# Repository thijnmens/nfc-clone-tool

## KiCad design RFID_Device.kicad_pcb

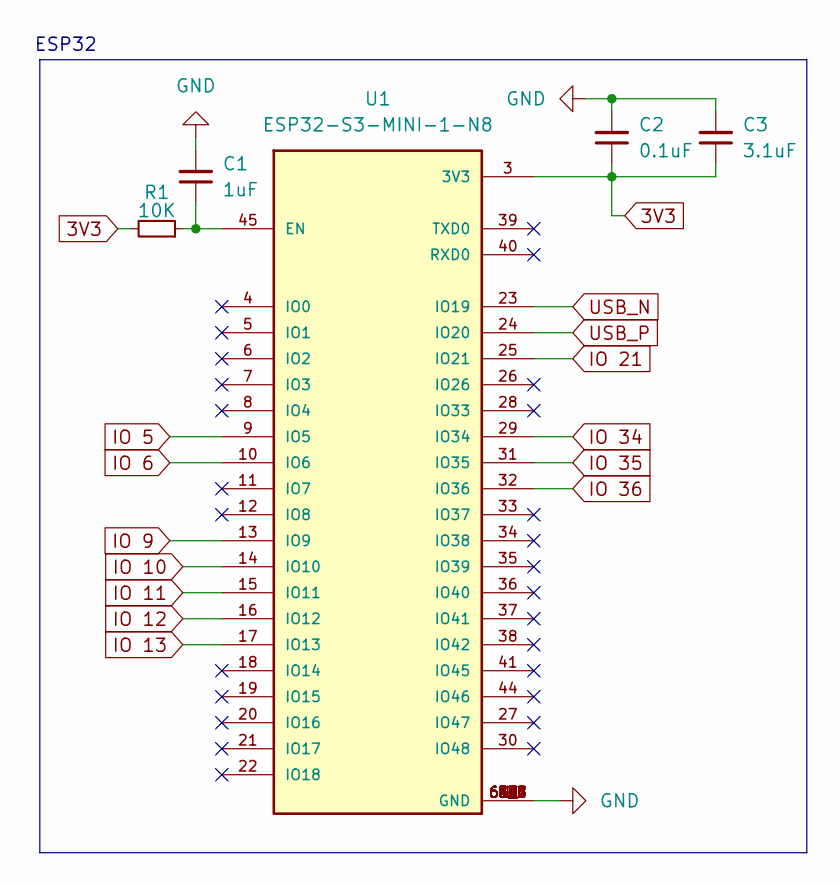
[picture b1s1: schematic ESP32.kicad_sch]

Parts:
C1: 1uF; C_0603_1608Metric; Manufacturer_Part_Number CC0603KRX5R8BB105; DigiKey_Part_Number 311-1445-1-ND
C2: 0.1uF; C_0603_1608Metric; Manufacturer_Part_Number CC0603KRX7R8BB104; DigiKey_Part_Number 311-1341-1-ND
C3: 3.1uF; C_0805_2012Metric; Manufacturer_Part_Number CC0805ZKY5V6BB335; DigiKey_Part_Number 311-1190-1-ND
R1: 10K; R_0402_1005Metric; Manufacturer_Part_Number RC0402JR-0710KL; DigiKey_Part_Number 311-10KJRCT-ND
U1: ESP32-S3-MINI-1-N8; XCVR_ESP32-S3-MINI-1-N8; Manufacturer_Part_Number ESP32-S3-MINI-1-N8; DigiKey_Part_Number 1965-ESP32-S3-MINI-1-N8CT-ND

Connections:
3V3: C2.1, C3.1, R1.2, U1.3 (3V3); also elsewhere on the board
GND: C1.2, C2.2, C3.2, U1.1 (GND), U1.2 (GND), U1.42 (GND), U1.43 (GND), U1.46 (GND), U1.47 (GND), U1.48 (GND), U1.49 (GND), U1.50 (GND), U1.51 (GND), U1.52 (GND), U1.53 (GND), U1.54 (GND), U1.55 (GND), U1.56 (GND), U1.57 (GND), U1.58 (GND), U1.59 (GND), U1.60 (GND), U1.61 (GND), U1.61_1 (GND), U1.61_2 (GND), U1.61_3 (GND), U1.61_4 (GND), U1.61_5 (GND), U1.61_6 (GND), U1.61_7 (GND), U1.61_8 (GND), U1.62 (GND), U1.63 (GND), U1.64 (GND), U1.65 (GND); also elsewhere on the board
IO 5: U1.9 (IO5); also elsewhere on the board
IO 6: U1.10 (IO6); also elsewhere on the board
IO 9: U1.13 (IO9); also elsewhere on the board
IO 10: U1.14 (IO10); also elsewhere on the board
IO 11: U1.15 (IO11); also elsewhere on the board
IO 12: U1.16 (IO12); also elsewhere on the board
IO 13: U1.17 (IO13); also elsewhere on the board
IO 21: U1.25 (IO21); also elsewhere on the board
IO 34: U1.29 (IO34); also elsewhere on the board
IO 35: U1.31 (IO35); also elsewhere on the board
IO 36: U1.32 (IO36); also elsewhere on the board
unnamed: C1.1, R1.1, U1.45 (EN)
USB_N: U1.23 (IO19); also elsewhere on the board
USB_P: U1.24 (IO20); also elsewhere on the board

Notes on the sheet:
ESP32

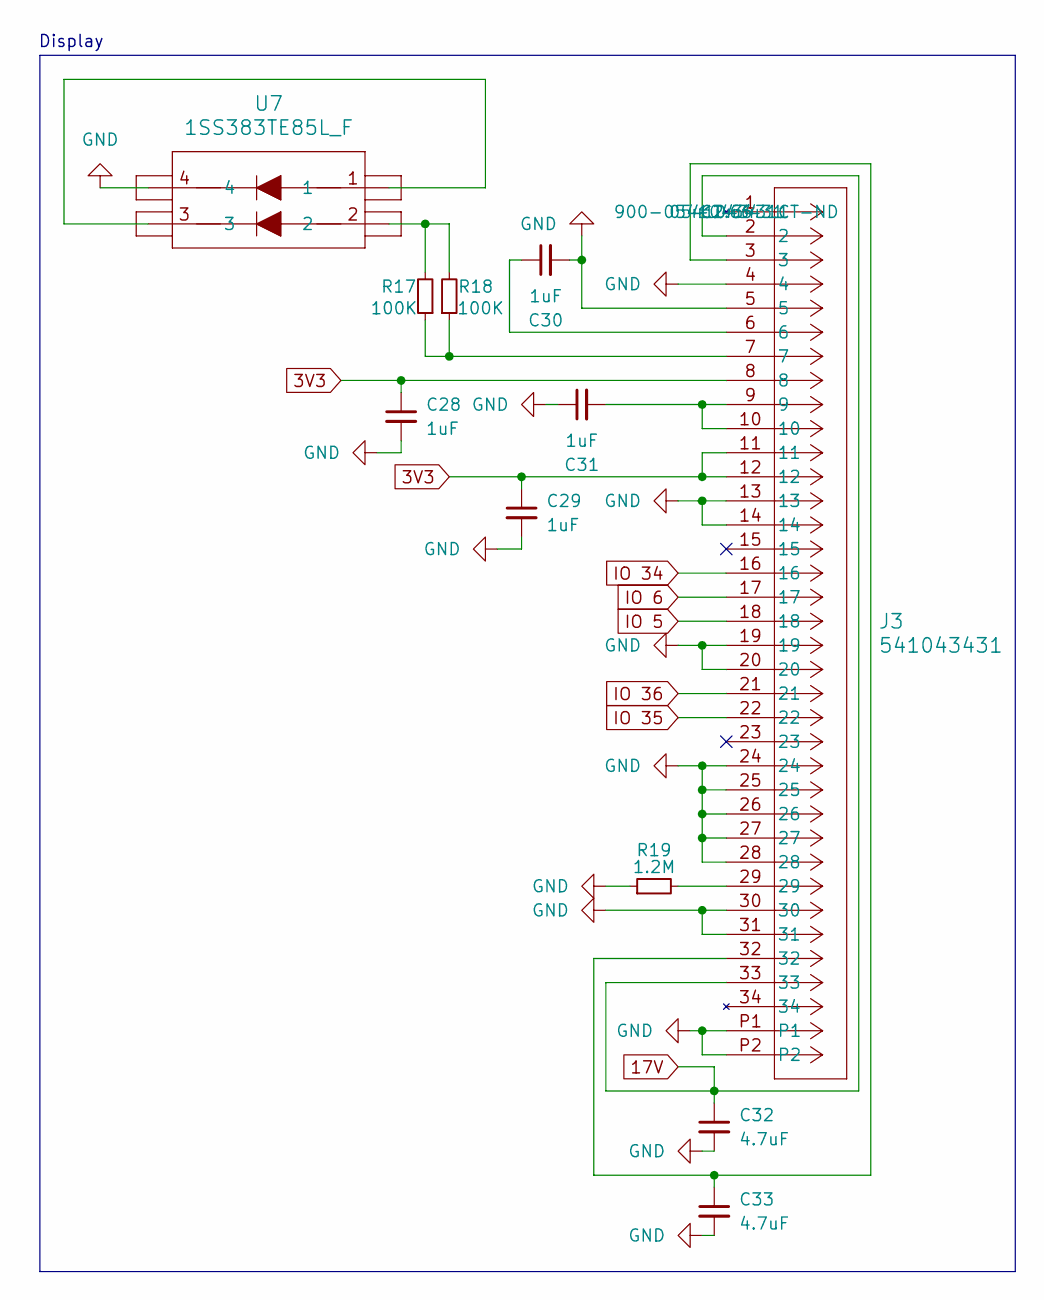
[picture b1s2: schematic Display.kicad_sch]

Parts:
C28, C29, C30, C31: 1uF; C_0603_1608Metric; Manufacturer_Part_Number CC0603KRX5R8BB105; DigiKey_Part_Number 311-1445-1-ND
C32, C33: 4.7uF; C_0805_2012Metric; Manufacturer_Part_Number CL21A475KAQNNNE; DigiKey_Part_Number 1276-1244-1-ND
J3: 541043431; CON_541043431_MOL; Manufacturer_Part_Number 0541043431; DigiKey_Part_Number 900-0541043431CT-ND
R17, R18: 100K; R_0402_1005Metric; Manufacturer_Part_Number RC0402FR-07100KL; DigiKey_Part_Number 311-100KLRCT-ND
R19: 1.2M; R_0402_1005Metric; Manufacturer_Part_Number AC0402FR-071M2L; DigiKey_Part_Number YAG5649CT-ND
U7: 1SS383TE85L_F; USQ_TOS; Manufacturer_Part_Number 1SS383(TE85L,F); DigiKey_Part_Number 1SS383(TE85LF)CT-ND

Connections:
3V3: C28.1, C29.1, J3.8, J3.11, J3.12; also elsewhere on the board
17V: C32.1, J3.2, J3.33; also elsewhere on the board
GND: C28.2, C29.2, C30.2, C31.1, C32.2, C33.2, J3.4, J3.5, J3.13, J3.14, J3.19, J3.20, J3.24, J3.25, J3.26, J3.27, J3.28, J3.30, J3.31, J3.P1, J3.P2, R19.1, U7.4; also elsewhere on the board
IO 5: J3.18; also elsewhere on the board
IO 6: J3.17; also elsewhere on the board
IO 34: J3.16; also elsewhere on the board
IO 35: J3.22; also elsewhere on the board
IO 36: J3.21; also elsewhere on the board
unnamed: C30.1, J3.6
unnamed: C31.2, J3.9, J3.10
unnamed: C33.1, J3.3, J3.32
unnamed: J3.7, R17.1, R18.1
unnamed: J3.29, R19.2
unnamed: R17.2, R18.2, U7.2
unnamed: U7.1, U7.3

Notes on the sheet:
Display

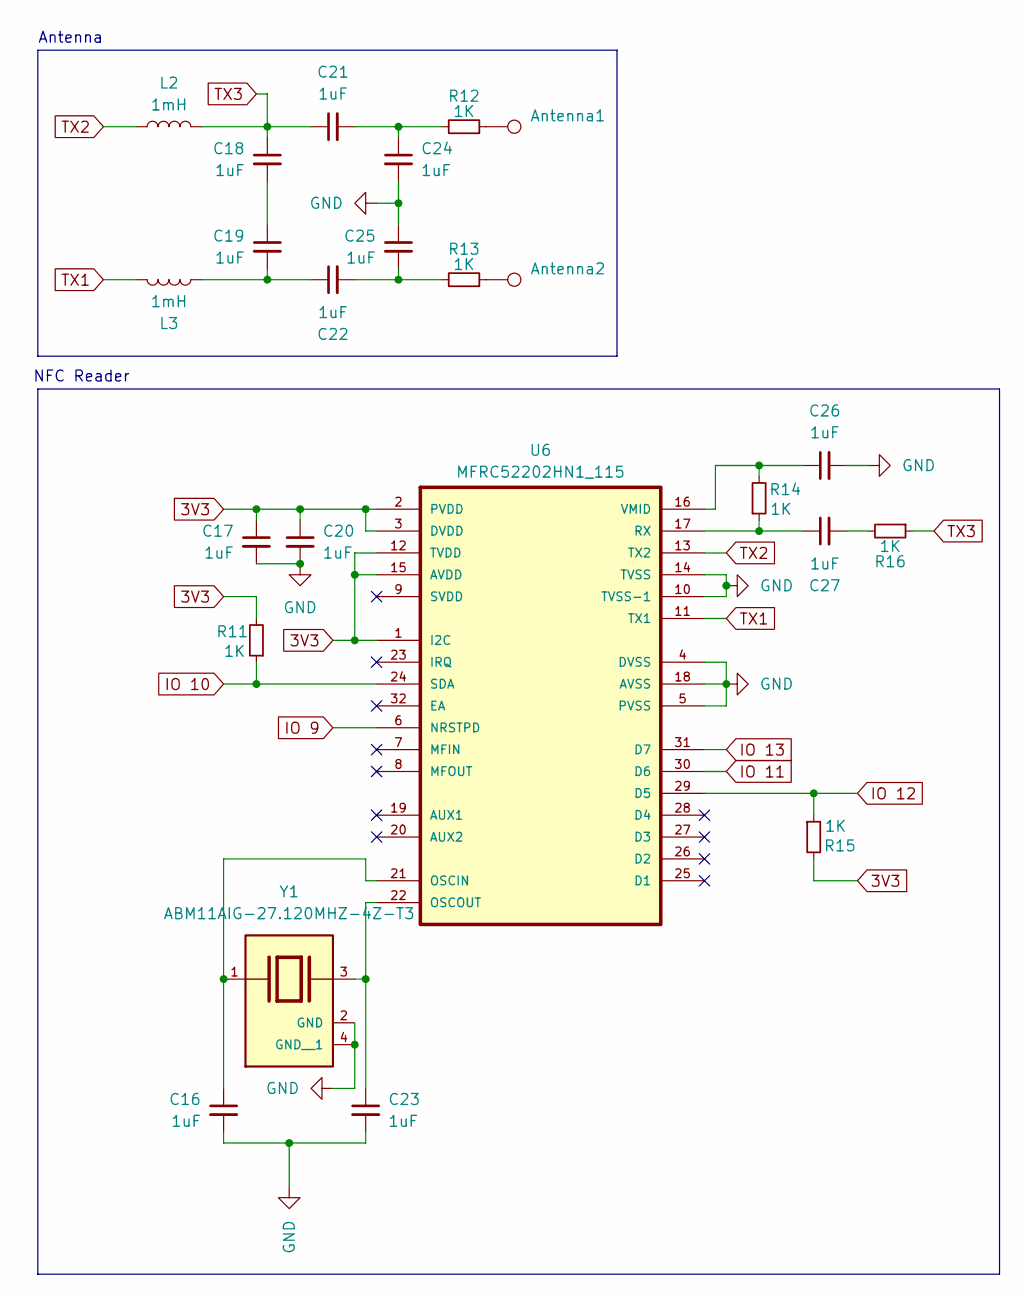
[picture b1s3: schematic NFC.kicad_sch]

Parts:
Antenna1, Antenna2: TestPoint_Pad_D2.0mm
C16, C17, C18, C19, C20, C21, C22, C23, C24, C25, C26, C27: 1uF; C_0603_1608Metric; Manufacturer_Part_Number CC0603KRX5R8BB105; DigiKey_Part_Number 311-1445-1-ND
L2, L3: 1mH; L_1210_3225Metric; Manufacturer_Part_Number CBC3225T102KR; DigiKey_Part_Number 587-3214-1-ND
R11, R12, R13, R14, R15, R16: 1K; R_1206_3216Metric; Manufacturer_Part_Number RNCP1206FTD1K00; DigiKey_Part_Number RNCP1206FTD1K00CT-ND
U6: MFRC52202HN1_115; HVQFN-32-1EP_5x5mm_P0.5mm_EP3.1x3.1mm; Manufacturer_Part_Number MFRC52202HN1,115; DigiKey_Part_Number 568-15200-1-ND
Y1: ABM11AIG-27.120MHZ-4Z-T3; XTAL_ABM11AIG-27.120MHZ-4Z-T3; Manufacturer_Part_Number ABM11AIG-27.120MHZ-4Z-T3; DigiKey_Part_Number 535-13376-1-ND

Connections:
3V3: C17.1, C20.1, R11.2, R15.2, U6.1 (I2C), U6.2 (PVDD), U6.3 (DVDD), U6.12 (TVDD), U6.15 (AVDD); also elsewhere on the board
GND: C16.2, C17.2, C20.2, C23.2, C24.2, C25.1, C26.2, U6.4 (DVSS), U6.5 (PVSS), U6.10 (TVSS-1), U6.14 (TVSS), U6.18 (AVSS), Y1.2 (GND), Y1.4 (GND__1); also elsewhere on the board
IO 9: U6.6 (NRSTPD); also elsewhere on the board
IO 10: R11.1, U6.24 (SDA); also elsewhere on the board
IO 11: U6.30 (D6); also elsewhere on the board
IO 12: R15.1, U6.29 (D5); also elsewhere on the board
IO 13: U6.31 (D7); also elsewhere on the board
unnamed: Antenna1.1, R12.1
unnamed: Antenna2.1, R13.1
unnamed: C18.2, C19.1
unnamed: C19.2, C22.1, L3.2
unnamed: C21.2, C24.1, R12.2
unnamed: C22.2, C25.2, R13.2
unnamed: C27.2, R16.2
unnamed: C16.1, U6.21 (OSCIN), Y1.1
unnamed: C23.1, U6.22 (OSCOUT), Y1.3
unnamed: C27.1, R14.1, U6.17 (RX)
unnamed: C26.1, R14.2, U6.16 (VMID)
TX1: L3.1, U6.11 (TX1)
TX2: L2.1, U6.13 (TX2)
TX3: C18.1, C21.1, L2.2, R16.1

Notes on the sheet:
NFC Reader
Antenna

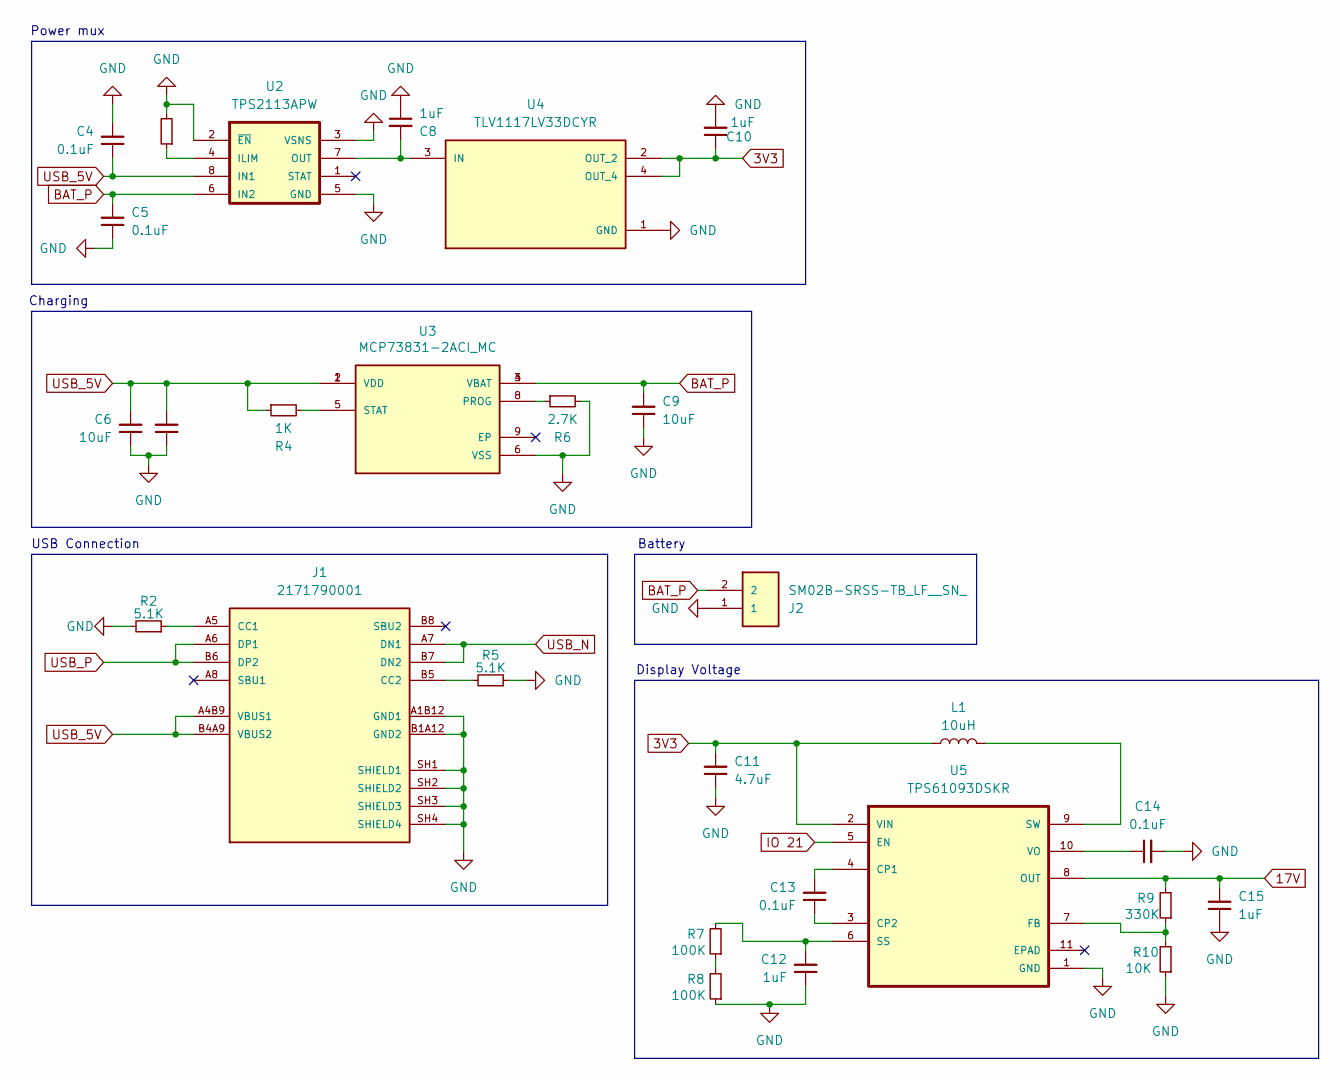
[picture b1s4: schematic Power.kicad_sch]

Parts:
C4, C5, C7, C13, C14: 0.1uF; C_0603_1608Metric; Manufacturer_Part_Number CC0603KRX7R8BB104; DigiKey_Part_Number 311-1341-1-ND
C6, C9: 10uF; C_0805_2012Metric; Manufacturer_Part_Number CL21A106KOQNNNG; DigiKey_Part_Number 1276-6455-1-ND
C8, C10, C12, C15: 1uF; C_0603_1608Metric; Manufacturer_Part_Number CC0603KRX5R8BB105; DigiKey_Part_Number 311-1445-1-ND
C11: 4.7uF; C_0805_2012Metric; Manufacturer_Part_Number CL21A475KAQNNNE; DigiKey_Part_Number 1276-1244-1-ND
J1: 2171790001; MOLEX_2171790001; Manufacturer_Part_Number 2171790001; DigiKey_Part_Number 900-2171790001CT-ND
J2: SM02B-SRSS-TB_LF__SN_; Manufacturer_Part_Number SM02B-SRSS-TB; DigiKey_Part_Number 455-SM02B-SRSS-TBCT-ND
L1: 10uH; L_0805_2012Metric; Manufacturer_Part_Number LBR2012T100K; DigiKey_Part_Number 587-2045-1-ND
R2, R5: 5.1K; R_0402_1005Metric; Manufacturer_Part_Number ERA-2AEB512X; DigiKey_Part_Number P5.1KDCCT-ND
R3, R10: 10K; R_0402_1005Metric; Manufacturer_Part_Number RC0402JR-0710KL; DigiKey_Part_Number 311-10KJRCT-ND
R4: 1K; R_1206_3216Metric; Manufacturer_Part_Number RNCP1206FTD1K00; DigiKey_Part_Number RNCP1206FTD1K00CT-ND
R6: 2.7K; R_1206_3216Metric; Manufacturer_Part_Number RC1206FR-072K7L; DigiKey_Part_Number 311-2.70KFRCT-ND
R7, R8: 100K; R_0402_1005Metric; Manufacturer_Part_Number RC0402FR-07100KL; DigiKey_Part_Number 311-100KLRCT-ND
R9: 330K; R_1206_3216Metric; Manufacturer_Part_Number CRGCQ1206F330K; DigiKey_Part_Number A129840CT-ND
U2: TPS2113APW; SOP65P640X120-8N; Manufacturer_Part_Number TPS2113APW; DigiKey_Part_Number 296-34596-5-ND
U3: MCP73831-2ACI_MC; SON50P200X300X100-9N; Manufacturer_Part_Number MCP73831-2ACI/MC; DigiKey_Part_Number MCP73831-2ACI/MC-ND
U4: TLV1117LV33DCYR; VREG_TLV1117LV33DCYR; Manufacturer_Part_Number TLV1117LV33DCYR; DigiKey_Part_Number 296-28778-1-ND
U5: TPS61093DSKR; SON50P250X250X80-11N; Manufacturer_Part_Number TPS61093DSKR; DigiKey_Part_Number 296-39430-1-ND

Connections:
3V3: C10.1, C11.2, L1.1, U4.2 (OUT_2), U4.4 (OUT_4), U5.2 (VIN); also elsewhere on the board
17V: C15.2, R9.2, U5.8 (OUT); also elsewhere on the board
BAT_P: C5.2, C9.2, J2.2, U2.6 (IN2), U3.3 (VBAT), U3.4 (VBAT)
GND: C4.2, C5.1, C6.1, C7.1, C8.1, C9.1, C10.2, C11.1, C12.1, C14.2, C15.1, J1.A1B12 (GND1), J1.B1A12 (GND2), J1.SH1 (SHIELD1), J1.SH2 (SHIELD2), J1.SH3 (SHIELD3), J1.SH4 (SHIELD4), J2.1, R2.2, R3.2, R5.1, R6.2, R8.1, R10.1, U2.2 (~EN), U2.3 (VSNS), U2.5 (GND), U3.6 (VSS), U4.1 (GND), U5.1 (GND); also elsewhere on the board
IO 21: U5.5 (EN); also elsewhere on the board
unnamed: J1.A5 (CC1), R2.1
unnamed: J1.B5 (CC2), R5.2
unnamed: R7.1, R8.2
unnamed: R3.1, U2.4 (ILIM)
unnamed: C8.2, U2.7 (OUT), U4.3 (IN)
unnamed: R6.1, U3.8 (PROG)
unnamed: R4.2, U3.5 (STAT)
unnamed: C13.2, U5.4 (CP1)
unnamed: C13.1, U5.3 (CP2)
unnamed: R9.1, R10.2, U5.7 (FB)
unnamed: C12.2, R7.2, U5.6 (SS)
unnamed: L1.2, U5.9 (SW)
unnamed: C14.1, U5.10 (VO)
USB_5V: C4.1, C6.2, C7.2, J1.A4B9 (VBUS1), J1.B4A9 (VBUS2), R4.1, U2.8 (IN1), U3.1 (VDD), U3.2 (VDD)
USB_N: J1.A7 (DN1), J1.B7 (DN2); also elsewhere on the board
USB_P: J1.A6 (DP1), J1.B6 (DP2); also elsewhere on the board

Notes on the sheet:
Charging
Power mux
USB Connection
Battery
Display Voltage

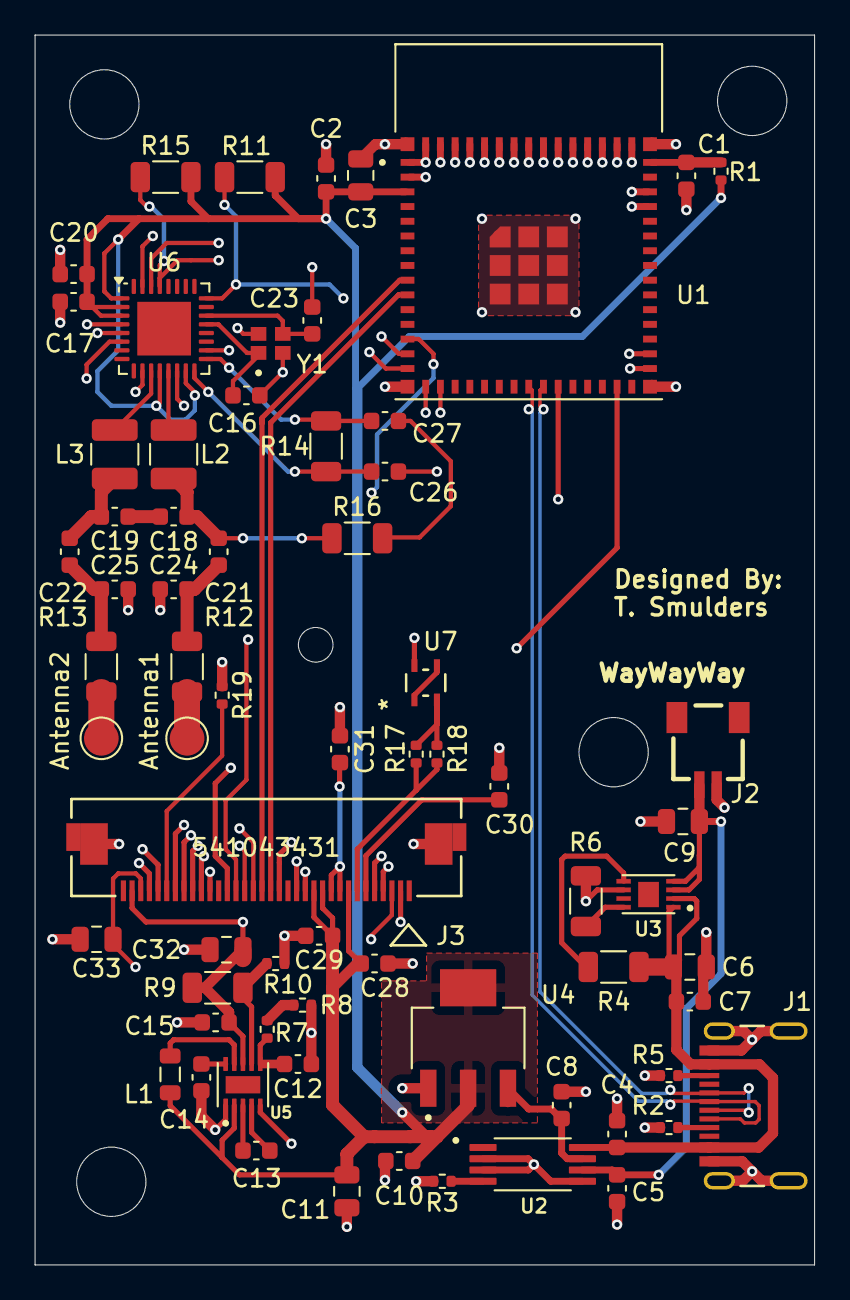
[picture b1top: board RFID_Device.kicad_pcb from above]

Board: 4 copper layers, 45.0 x 71.0 mm, 68 parts (0 on the bottom side), 53 nets.

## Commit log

2025-02-28 Add gitignore
2025-02-28 Add device schematic
2025-03-01 Create PCB
2025-03-01 Fix minor design mistakes
2025-05-15 Remove everything
2025-05-15 Add debug screen
